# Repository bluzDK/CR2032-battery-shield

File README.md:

Bluz CR2032 Battery Shield Hardware Files
==========
Bluz is a Development Kit (DK) that implements the Wiring language and talks to the [Particle](https://www.particle.io/) cloud through Bluetooth Low Energy. It can be accessed through a REST API and programmed from a Web IDE.

These files have been made available online through a [Creative Commons Attribution-ShareAlike 3.0](http://creativecommons.org/licenses/by-sa/3.0/) license.

You are welcome to distribute, remix, and use these files for commercial purposes. If you do so, please attribute the original design to Bluz both on the website and on the physical packaging of the product or in the instruction manual. All derivative works must be published under the same or a similar license.

All items are subject to change over time as the product is designed, so make sure you are always looking at the latest information by pulling often.

##Sections
<b>BOM</b>: Current Bill of Materials for the battery shield.

<b>Datasheets</b>: Datasheets for all major parts on the board.

<b>HW Design</b>: Schematics, board layouts, and other design files.

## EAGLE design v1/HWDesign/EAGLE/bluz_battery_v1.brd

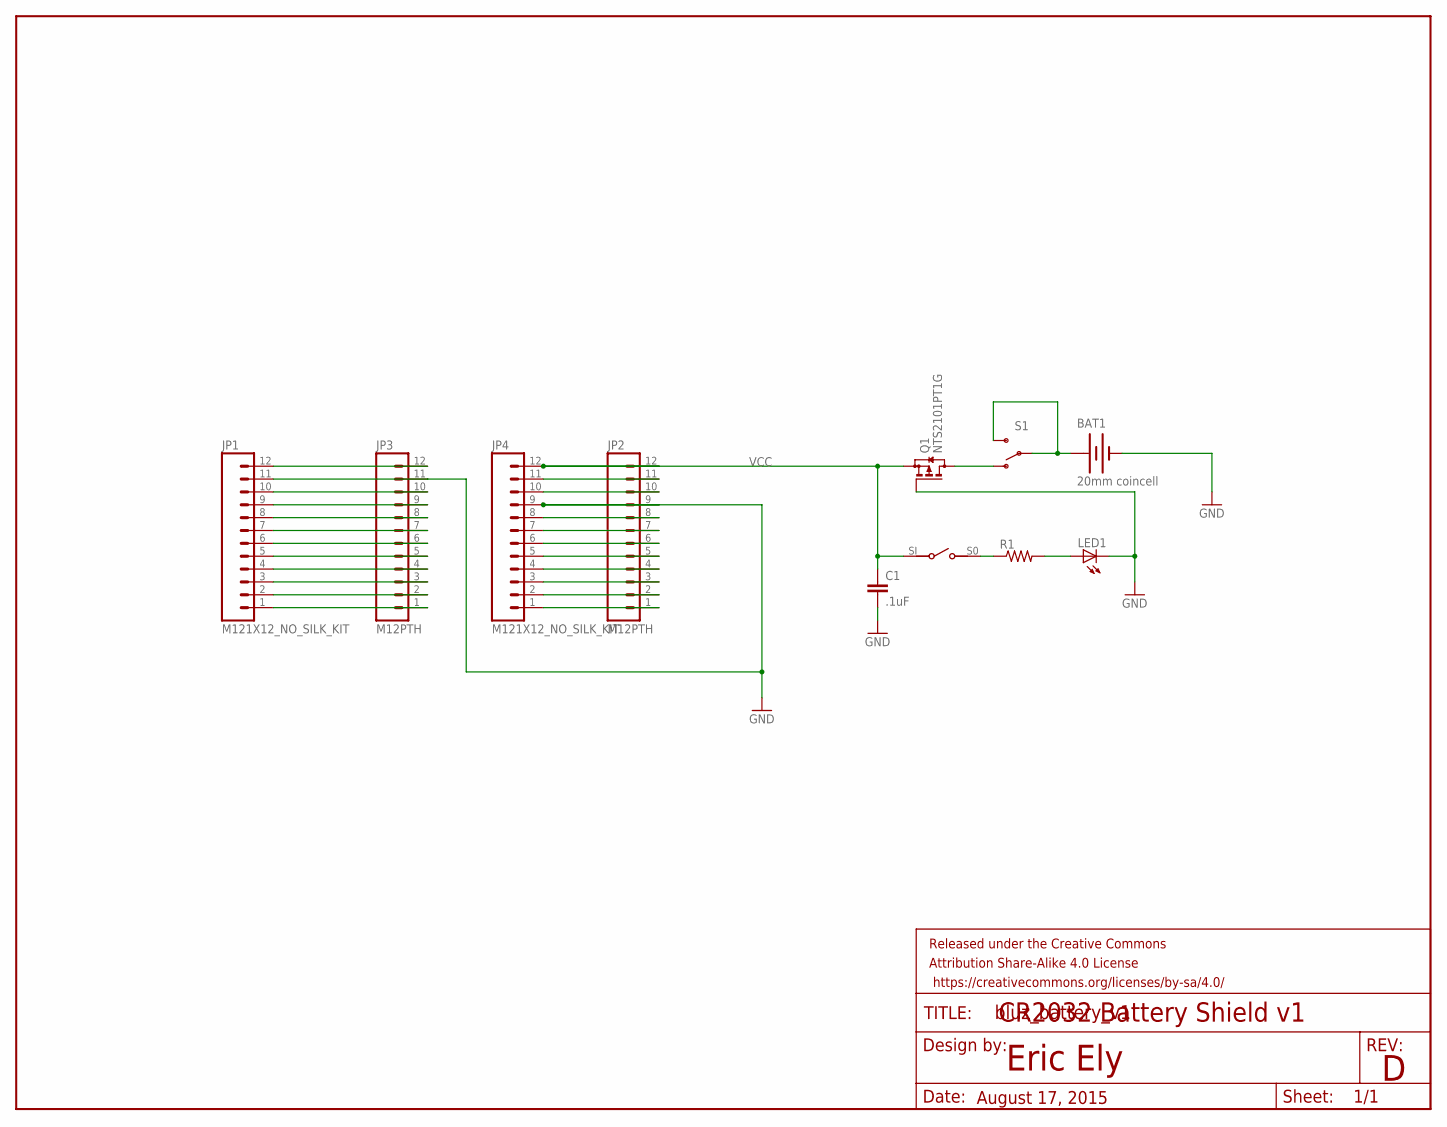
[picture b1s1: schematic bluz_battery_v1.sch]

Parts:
BAT1: 20mm coincell; BATTCON_20MM_4LEGS
C1: .1uF; 0603-CAP
FRAME1: FRAME-LETTER; CREATIVE_COMMONS
JP1, JP4: M121X12_NO_SILK_KIT; 1X12_NO_SILK_KIT
JP2, JP3: M12PTH; 1X12
LED1: LEDCHIPLED_0603; CHIPLED_0603
Q1: NTS2101PT1G; SOT323
R1: RESISTOR0603-RES; 0603-RES
S1: SWITCH-SPDTKIT; SWITCH-SPDT_KIT
S2: CHS-01TASMD; CHS-01TA

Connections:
GND: BAT1.2 (-), C1.2, JP1.11, JP2.9, JP3.11, JP4.9, LED1.C, Q1.1 (G)
unnamed: BAT1.1 (+), S1.2, S1.3 (S)
unnamed: JP1.1, JP3.1
unnamed: LED1.A, R1.2
unnamed: R1.1, S2.S0 (SO)
unnamed: Q1.3 (D), S1.1 (O)
unnamed: JP1.2, JP3.2
unnamed: JP1.3, JP3.3
unnamed: JP1.4, JP3.4
unnamed: JP1.5, JP3.5
unnamed: JP1.6, JP3.6
unnamed: JP1.7, JP3.7
unnamed: JP1.8, JP3.8
unnamed: JP1.9, JP3.9
unnamed: JP1.10, JP3.10
unnamed: JP1.12, JP3.12
unnamed: JP2.1, JP4.1
unnamed: JP2.2, JP4.2
unnamed: JP2.3, JP4.3
unnamed: JP2.4, JP4.4
unnamed: JP2.5, JP4.5
unnamed: JP2.6, JP4.6
unnamed: JP2.7, JP4.7
unnamed: JP2.8, JP4.8
unnamed: JP2.10, JP4.10
unnamed: JP2.11, JP4.11
VCC: C1.1, JP2.12, JP4.12, Q1.2 (S), S2.SI (S!)

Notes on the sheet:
Eric Ely
August 17, 2015
CR2032 Battery Shield v1

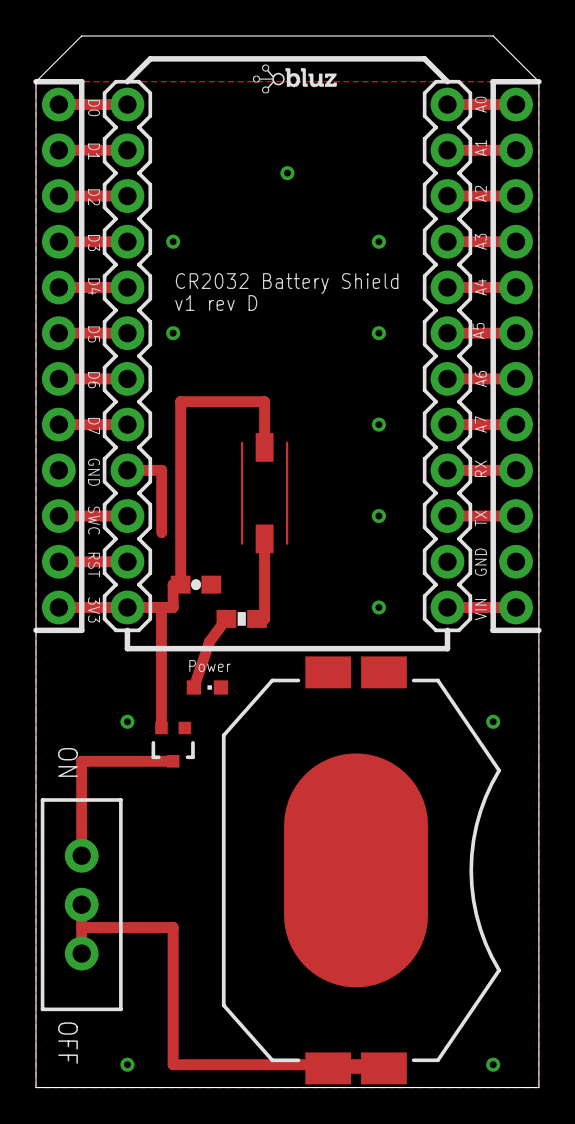
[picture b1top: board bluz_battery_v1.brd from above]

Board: 2 copper layers, 27.9 x 58.4 mm, 13 parts (0 on the bottom side), 27 nets.

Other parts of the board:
U$1: BLUZE_LOGO_LOW_RES

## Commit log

2015-07-01 initial hw files
2015-07-03 eagle files and scripts
2015-08-17 changed battery shield to have breakouts and moved switch
2015-09-13 updated slightly
2015-09-13 label headers properly

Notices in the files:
parts and their libraries:
SparkFun-Electromechanical: Licensing: Creative Commons ShareAlike 4.0 International - https://creativecommons.org/licenses/by-sa/4.0
SparkFun-Aesthetics: Released under the Creative Commons Attribution Share-Alike 4.0 License
SparkFun-Aesthetics: https://creativecommons.org/licenses/by-sa/4.0
